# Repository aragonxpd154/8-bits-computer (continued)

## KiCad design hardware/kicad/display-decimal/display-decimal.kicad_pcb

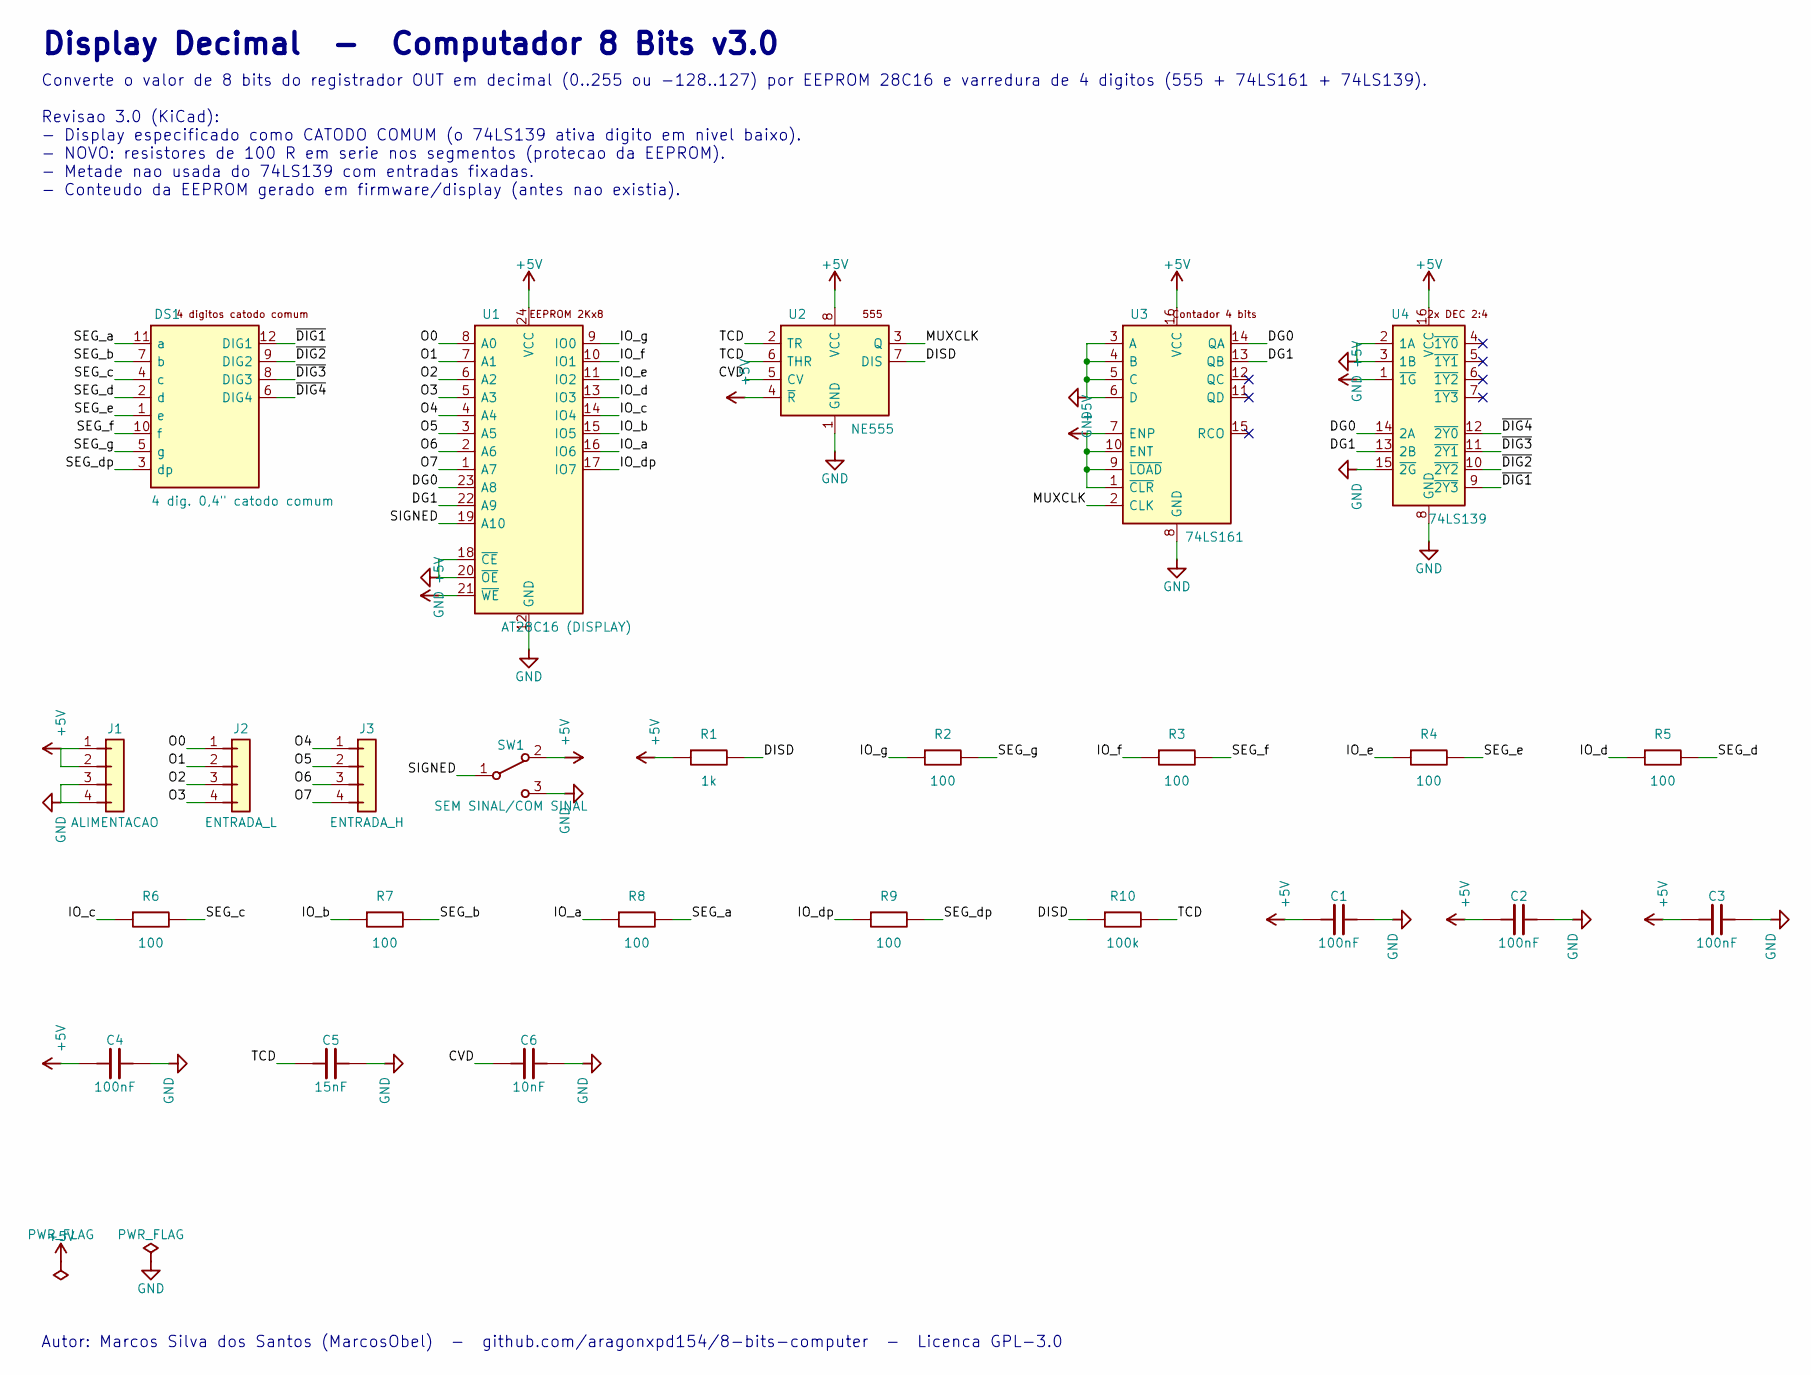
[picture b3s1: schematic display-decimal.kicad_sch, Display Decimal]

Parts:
C1, C2, C3, C4: 100nF; C_Disc_D5.0mm_W2.5mm_P5.00mm
C5: 15nF; C_Disc_D5.0mm_W2.5mm_P5.00mm
C6: 10nF; C_Disc_D5.0mm_W2.5mm_P5.00mm
DS1: 4 dig. 0,4" catodo comum; Display_7seg_4dig_0.4in
J1: ALIMENTACAO; PinHeader_1x04_P2.54mm_Vertical
J2: ENTRADA_L; PinHeader_1x04_P2.54mm_Vertical
J3: ENTRADA_H; PinHeader_1x04_P2.54mm_Vertical
R1: 1k; R_Axial_DIN0207_L6.3mm_D2.5mm_P10.16mm_Horizontal
R2, R3, R4, R5, R6, R7, R8, R9: 100; R_Axial_DIN0207_L6.3mm_D2.5mm_P10.16mm_Horizontal
R10: 100k; R_Axial_DIN0207_L6.3mm_D2.5mm_P10.16mm_Horizontal
SW1: SEM SINAL/COM SINAL; SW_Slide-03_Wuerth-WS-SLTV_10x2.5x6.4_P2.54mm
U1: AT28C16 (DISPLAY); DIP-24_W15.24mm_LongPads
U2: NE555; DIP-8_W7.62mm_LongPads
U3: 74LS161; DIP-16_W7.62mm_LongPads
U4: 74LS139; DIP-16_W7.62mm_LongPads

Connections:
+5V: C1.1, C2.1, C3.1, C4.1, J1.1, J1.2, R1.1, SW1.2 (A), U1.21 (~WE), U1.24 (VCC), U2.4 (~R), U2.8 (VCC), U3.1 (~CLR), U3.7 (ENP), U3.9 (~LOAD), U3.10 (ENT), U3.16 (VCC), U4.1 (~1G), U4.16 (VCC)
CVD: C6.1, U2.5 (CV)
DG0: U1.23 (A8), U3.14 (QA), U4.14 (2A)
DG1: U1.22 (A9), U3.13 (QB), U4.13 (2B)
DISD: R1.2, R10.1, U2.7 (DIS)
GND: C1.2, C2.2, C3.2, C4.2, C5.2, C6.2, J1.3, J1.4, SW1.3 (B), U1.12 (GND), U1.18 (~CE), U1.20 (~OE), U2.1 (GND), U3.3 (A), U3.4 (B), U3.5 (C), U3.6 (D), U3.8 (GND), U4.2 (1A), U4.3 (1B), U4.8 (GND), U4.15 (~2G)
IO_a: R8.1, U1.16 (IO6)
IO_b: R7.1, U1.15 (IO5)
IO_c: R6.1, U1.14 (IO4)
IO_d: R5.1, U1.13 (IO3)
IO_dp: R9.1, U1.17 (IO7)
IO_e: R4.1, U1.11 (IO2)
IO_f: R3.1, U1.10 (IO1)
IO_g: R2.1, U1.9 (IO0)
MUXCLK: U2.3 (Q), U3.2 (CLK)
O0: J2.1, U1.8 (A0)
O1: J2.2, U1.7 (A1)
O2: J2.3, U1.6 (A2)
O3: J2.4, U1.5 (A3)
O4: J3.1, U1.4 (A4)
O5: J3.2, U1.3 (A5)
O6: J3.3, U1.2 (A6)
O7: J3.4, U1.1 (A7)
SEG_a: DS1.11 (a), R8.2
SEG_b: DS1.7 (b), R7.2
SEG_c: DS1.4 (c), R6.2
SEG_d: DS1.2 (d), R5.2
SEG_dp: DS1.3 (dp), R9.2
SEG_e: DS1.1 (e), R4.2
SEG_f: DS1.10 (f), R3.2
SEG_g: DS1.5 (g), R2.2
SIGNED: SW1.1 (COM), U1.19 (A10)
TCD: C5.1, R10.2, U2.2 (TR), U2.6 (THR)
~DIG1: DS1.12 (DIG1), U4.9 (~2Y3)
~DIG2: DS1.9 (DIG2), U4.10 (~2Y2)
~DIG3: DS1.8 (DIG3), U4.11 (~2Y1)
~DIG4: DS1.6 (DIG4), U4.12 (~2Y0)

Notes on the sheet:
Display Decimal - Computador 8 Bits v3.0
Converte o valor de 8 bits do registrador OUT em decimal (0..255 ou -128..127) por EEPROM 28C16 e varredura de 4 digitos (555 + 74LS161 + 74LS139). Revisao 3.0 (KiCad): - Display especificado como CATODO COMUM (o 74LS139 ativa digito em nivel baixo). - NOVO: resistores de 100 R em serie nos segment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
Autor: Marcos Silva dos Santos (MarcosObel) - github.com/aragonxpd154/8-bits-computer - Licenca GPL-3.0

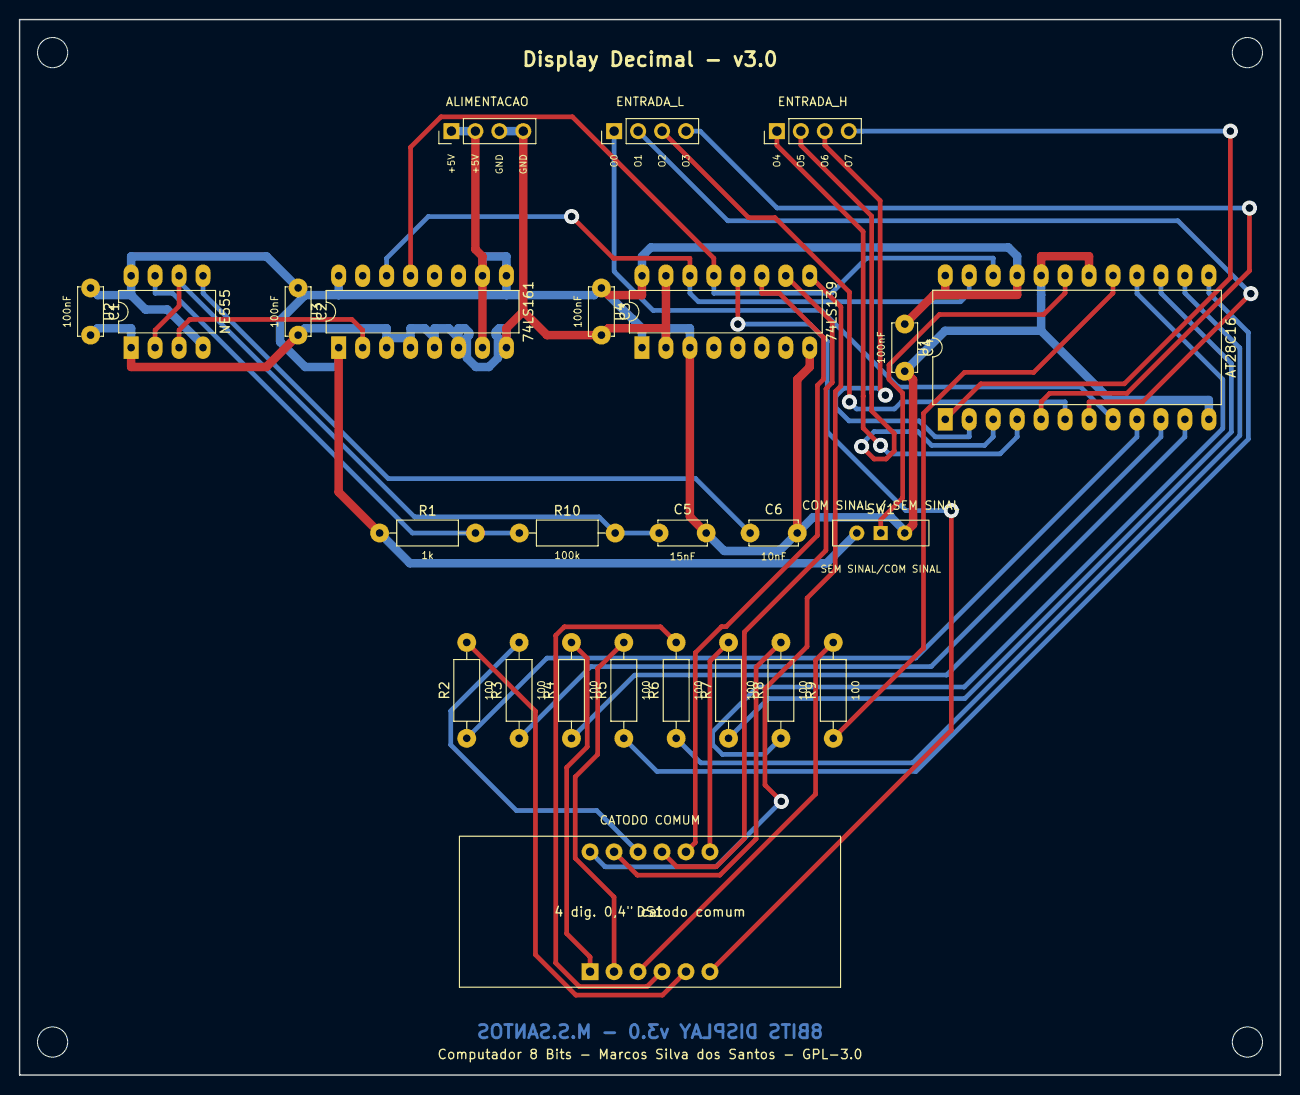
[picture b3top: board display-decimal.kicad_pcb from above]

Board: 2 copper layers, 133.7 x 111.9 mm, 29 parts (0 on the bottom side), 37 nets.

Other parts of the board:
H1, H2, H3, H4: MountingHole_3.2mm_M3

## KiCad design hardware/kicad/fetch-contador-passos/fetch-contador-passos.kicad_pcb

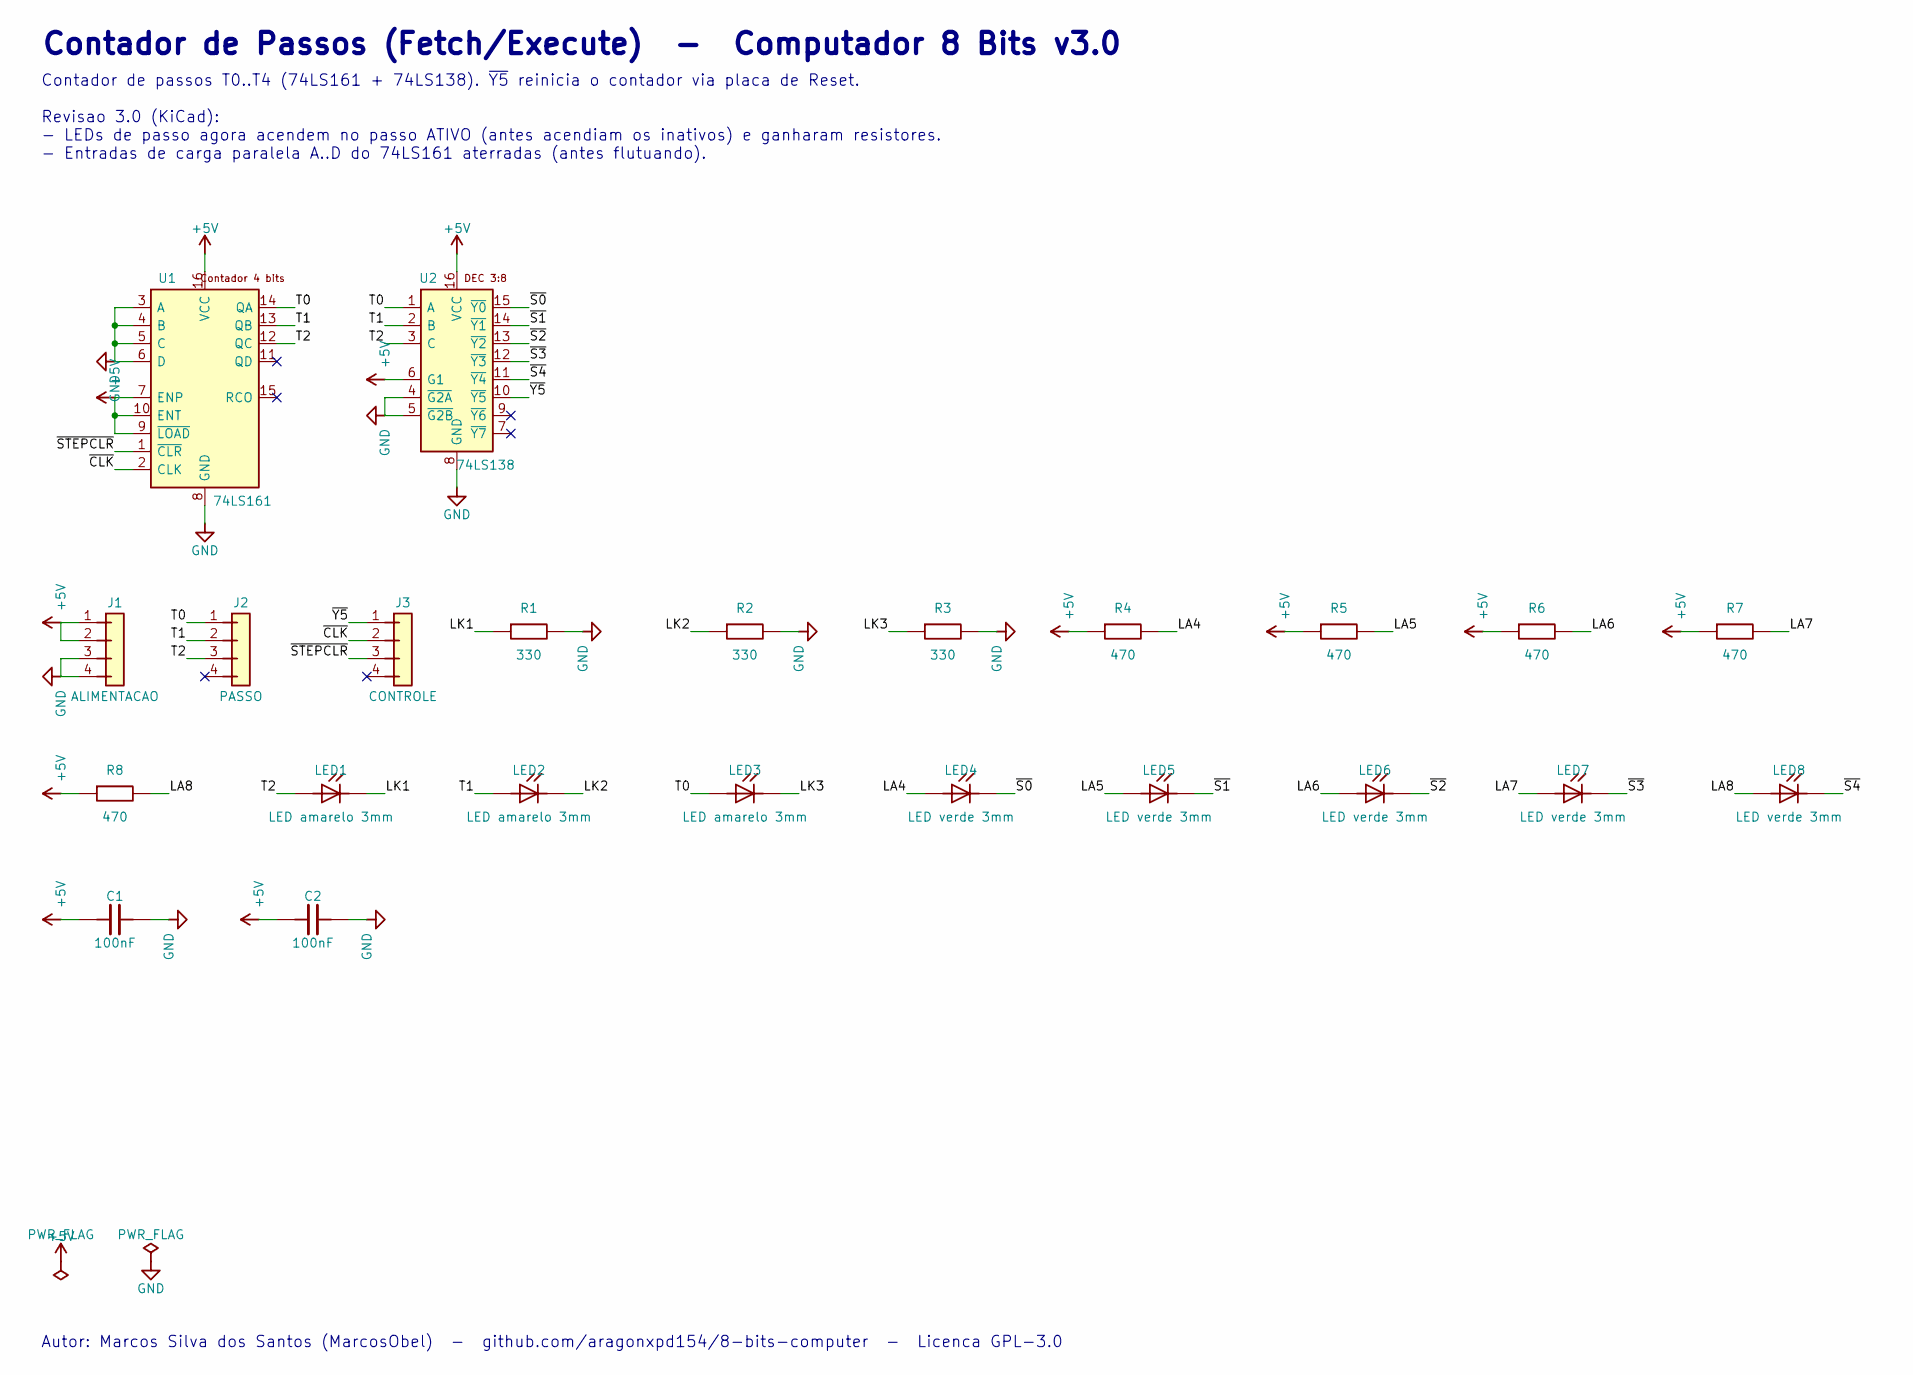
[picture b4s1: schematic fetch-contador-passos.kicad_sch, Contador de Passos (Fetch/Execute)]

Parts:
C1, C2: 100nF; C_Disc_D5.0mm_W2.5mm_P5.00mm
J1: ALIMENTACAO; PinHeader_1x04_P2.54mm_Vertical
J2: PASSO; PinHeader_1x04_P2.54mm_Vertical
J3: CONTROLE; PinHeader_1x04_P2.54mm_Vertical
LED1, LED2, LED3: LED amarelo 3mm; LED_D3.0mm
LED4, LED5, LED6, LED7, LED8: LED verde 3mm; LED_D3.0mm
R1, R2, R3: 330; R_Axial_DIN0207_L6.3mm_D2.5mm_P10.16mm_Horizontal
R4, R5, R6, R7, R8: 470; R_Axial_DIN0207_L6.3mm_D2.5mm_P10.16mm_Horizontal
U1: 74LS161; DIP-16_W7.62mm_LongPads
U2: 74LS138; DIP-16_W7.62mm_LongPads

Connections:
+5V: C1.1, C2.1, J1.1, J1.2, R4.1, R5.1, R6.1, R7.1, R8.1, U1.7 (ENP), U1.9 (~LOAD), U1.10 (ENT), U1.16 (VCC), U2.6 (G1), U2.16 (VCC)
GND: C1.2, C2.2, J1.3, J1.4, R1.2, R2.2, R3.2, U1.3 (A), U1.4 (B), U1.5 (C), U1.6 (D), U1.8 (GND), U2.4 (~G2A), U2.5 (~G2B), U2.8 (GND)
LA4: LED4.2 (A), R4.2
LA5: LED5.2 (A), R5.2
LA6: LED6.2 (A), R6.2
LA7: LED7.2 (A), R7.2
LA8: LED8.2 (A), R8.2
LK1: LED1.1 (K), R1.1
LK2: LED2.1 (K), R2.1
LK3: LED3.1 (K), R3.1
T0: J2.1, LED3.2 (A), U1.14 (QA), U2.1 (A)
T1: J2.2, LED2.2 (A), U1.13 (QB), U2.2 (B)
T2: J2.3, LED1.2 (A), U1.12 (QC), U2.3 (C)
~CLK: J3.2, U1.2 (CLK)
~S0: LED4.1 (K), U2.15 (~Y0)
~S1: LED5.1 (K), U2.14 (~Y1)
~S2: LED6.1 (K), U2.13 (~Y2)
~S3: LED7.1 (K), U2.12 (~Y3)
~S4: LED8.1 (K), U2.11 (~Y4)
~STEPCLR: J3.3, U1.1 (~CLR)
~Y5: J3.1, U2.10 (~Y5)

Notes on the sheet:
Contador de Passos (Fetch/Execute) - Computador 8 Bits v3.0
Contador de passos T0..T4 (74LS161 + 74LS138). ~{Y5} reinicia o contador via placa de Reset. Revisao 3.0 (KiCad): - LEDs de passo agora acendem no passo ATIVO (antes acendiam os inativos) e ganharam resistores. - Entradas de carga paralela A..D do 74LS161 aterradas (antes flutuando).
Autor: Marcos Silva dos Santos (MarcosObel) - github.com/aragonxpd154/8-bits-computer - Licenca GPL-3.0

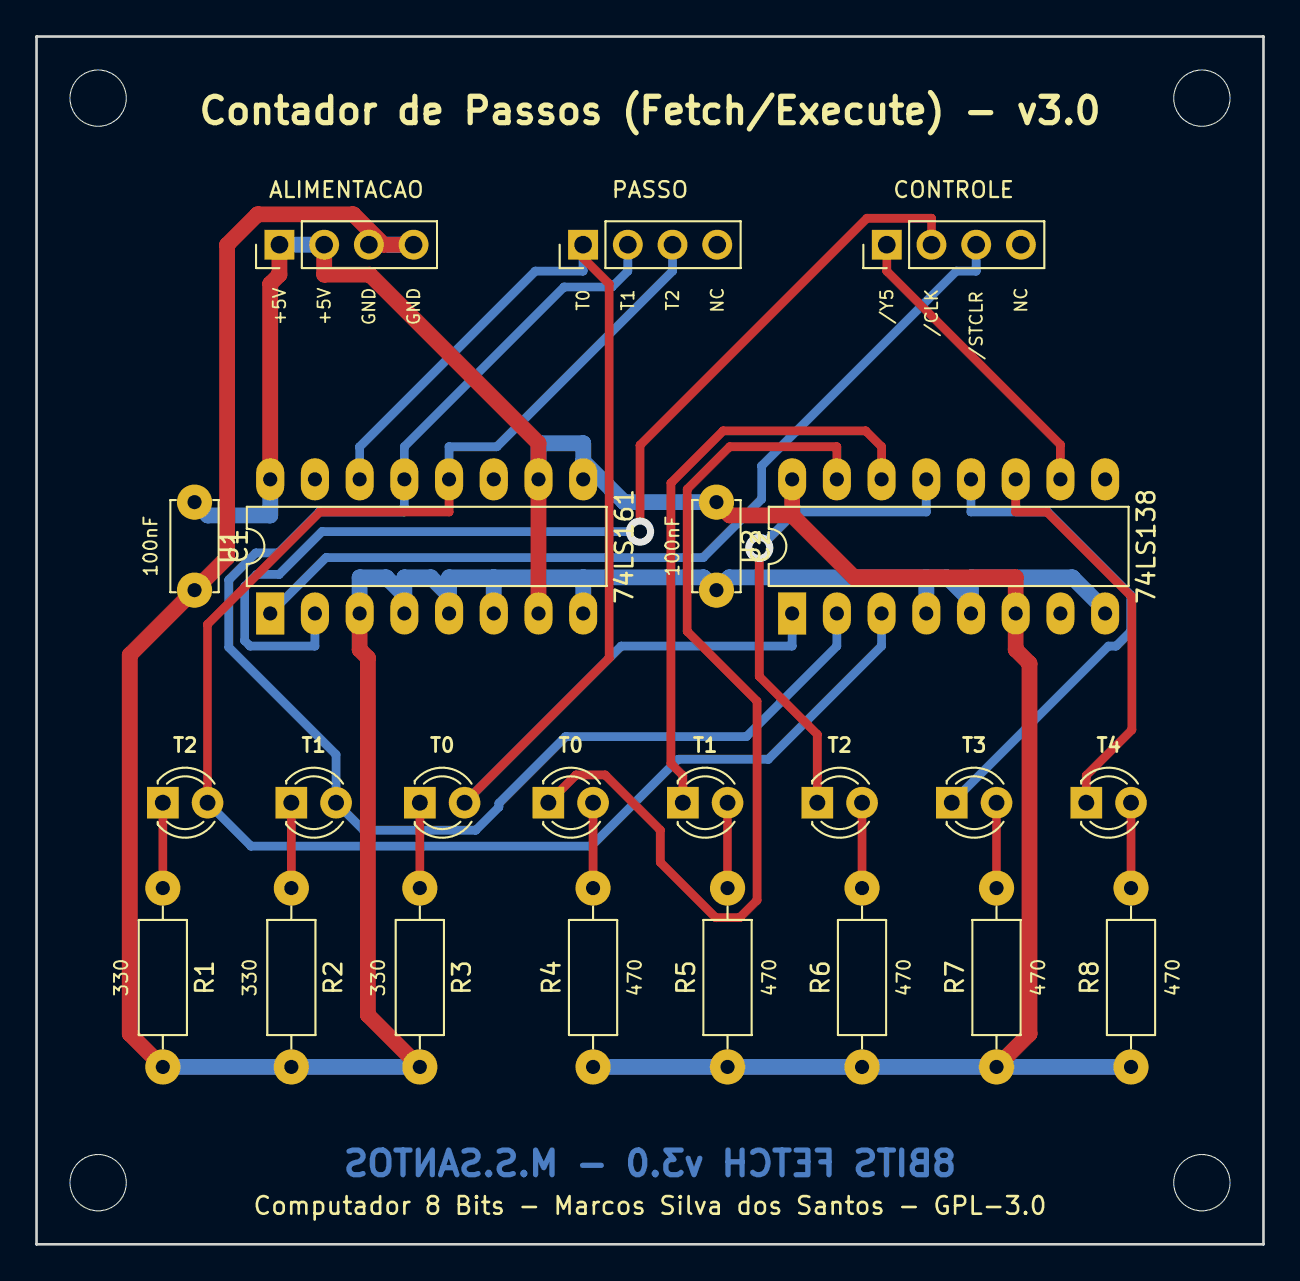
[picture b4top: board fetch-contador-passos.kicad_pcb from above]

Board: 2 copper layers, 69.7 x 68.6 mm, 27 parts (0 on the bottom side), 21 nets.

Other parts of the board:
H1, H2, H3, H4: MountingHole_3.2mm_M3

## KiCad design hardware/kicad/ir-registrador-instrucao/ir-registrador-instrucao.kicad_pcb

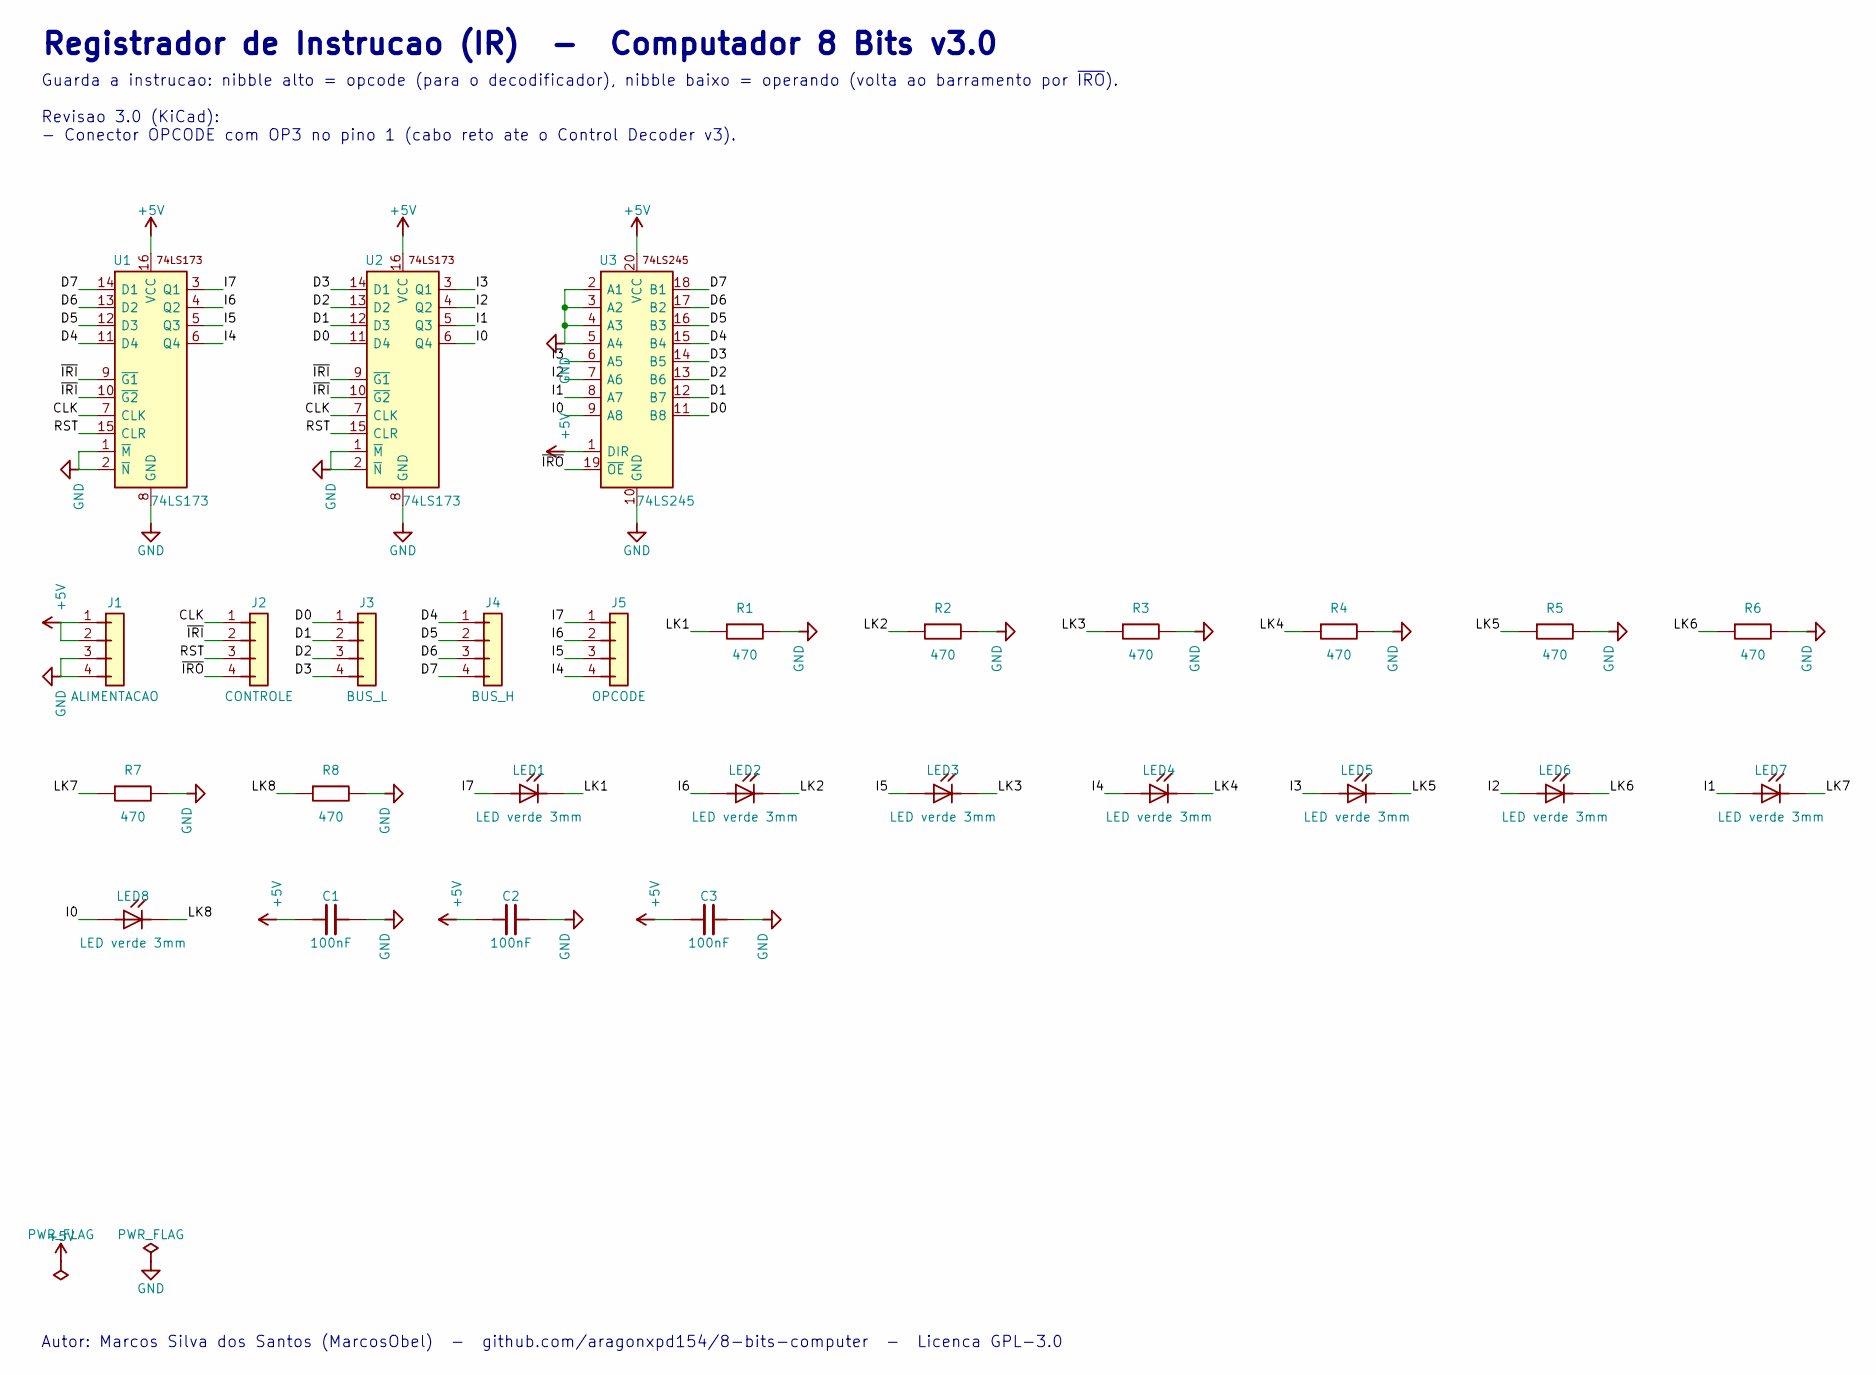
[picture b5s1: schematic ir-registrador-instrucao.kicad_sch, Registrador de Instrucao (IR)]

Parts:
C1, C2, C3: 100nF; C_Disc_D5.0mm_W2.5mm_P5.00mm
J1: ALIMENTACAO; PinHeader_1x04_P2.54mm_Vertical
J2: CONTROLE; PinHeader_1x04_P2.54mm_Vertical
J3: BUS_L; PinHeader_1x04_P2.54mm_Vertical
J4: BUS_H; PinHeader_1x04_P2.54mm_Vertical
J5: OPCODE; PinHeader_1x04_P2.54mm_Vertical
LED1, LED2, LED3, LED4, LED5, LED6, LED7, LED8: LED verde 3mm; LED_D3.0mm
R1, R2, R3, R4, R5, R6, R7, R8: 470; R_Axial_DIN0207_L6.3mm_D2.5mm_P10.16mm_Horizontal
U1, U2: 74LS173; DIP-16_W7.62mm_LongPads
U3: 74LS245; DIP-20_W7.62mm_LongPads

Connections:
+5V: C1.1, C2.1, C3.1, J1.1, J1.2, U1.16 (VCC), U2.16 (VCC), U3.1 (DIR), U3.20 (VCC)
CLK: J2.1, U1.7 (CLK), U2.7 (CLK)
D0: J3.1, U2.11 (D4), U3.11 (B8)
D1: J3.2, U2.12 (D3), U3.12 (B7)
D2: J3.3, U2.13 (D2), U3.13 (B6)
D3: J3.4, U2.14 (D1), U3.14 (B5)
D4: J4.1, U1.11 (D4), U3.15 (B4)
D5: J4.2, U1.12 (D3), U3.16 (B3)
D6: J4.3, U1.13 (D2), U3.17 (B2)
D7: J4.4, U1.14 (D1), U3.18 (B1)
GND: C1.2, C2.2, C3.2, J1.3, J1.4, R1.2, R2.2, R3.2, R4.2, R5.2, R6.2, R7.2, R8.2, U1.1 (~M), U1.2 (~N), U1.8 (GND), U2.1 (~M), U2.2 (~N), U2.8 (GND), U3.2 (A1), U3.3 (A2), U3.4 (A3), U3.5 (A4), U3.10 (GND)
I0: LED8.2 (A), U2.6 (Q4), U3.9 (A8)
I1: LED7.2 (A), U2.5 (Q3), U3.8 (A7)
I2: LED6.2 (A), U2.4 (Q2), U3.7 (A6)
I3: LED5.2 (A), U2.3 (Q1), U3.6 (A5)
I4: J5.4, LED4.2 (A), U1.6 (Q4)
I5: J5.3, LED3.2 (A), U1.5 (Q3)
I6: J5.2, LED2.2 (A), U1.4 (Q2)
I7: J5.1, LED1.2 (A), U1.3 (Q1)
LK1: LED1.1 (K), R1.1
LK2: LED2.1 (K), R2.1
LK3: LED3.1 (K), R3.1
LK4: LED4.1 (K), R4.1
LK5: LED5.1 (K), R5.1
LK6: LED6.1 (K), R6.1
LK7: LED7.1 (K), R7.1
LK8: LED8.1 (K), R8.1
RST: J2.3, U1.15 (CLR), U2.15 (CLR)
~IRI: J2.2, U1.9 (~G1), U1.10 (~G2), U2.9 (~G1), U2.10 (~G2)
~IRO: J2.4, U3.19 (~OE)

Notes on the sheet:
Registrador de Instrucao (IR) - Computador 8 Bits v3.0
Guarda a instrucao: nibble alto = opcode (para o decodificador), nibble baixo = operando (volta ao barramento por ~{IRO}). Revisao 3.0 (KiCad): - Conector OPCODE com OP3 no pino 1 (cabo reto ate o Control Decoder v3).
Autor: Marcos Silva dos Santos (MarcosObel) - github.com/aragonxpd154/8-bits-computer - Licenca GPL-3.0

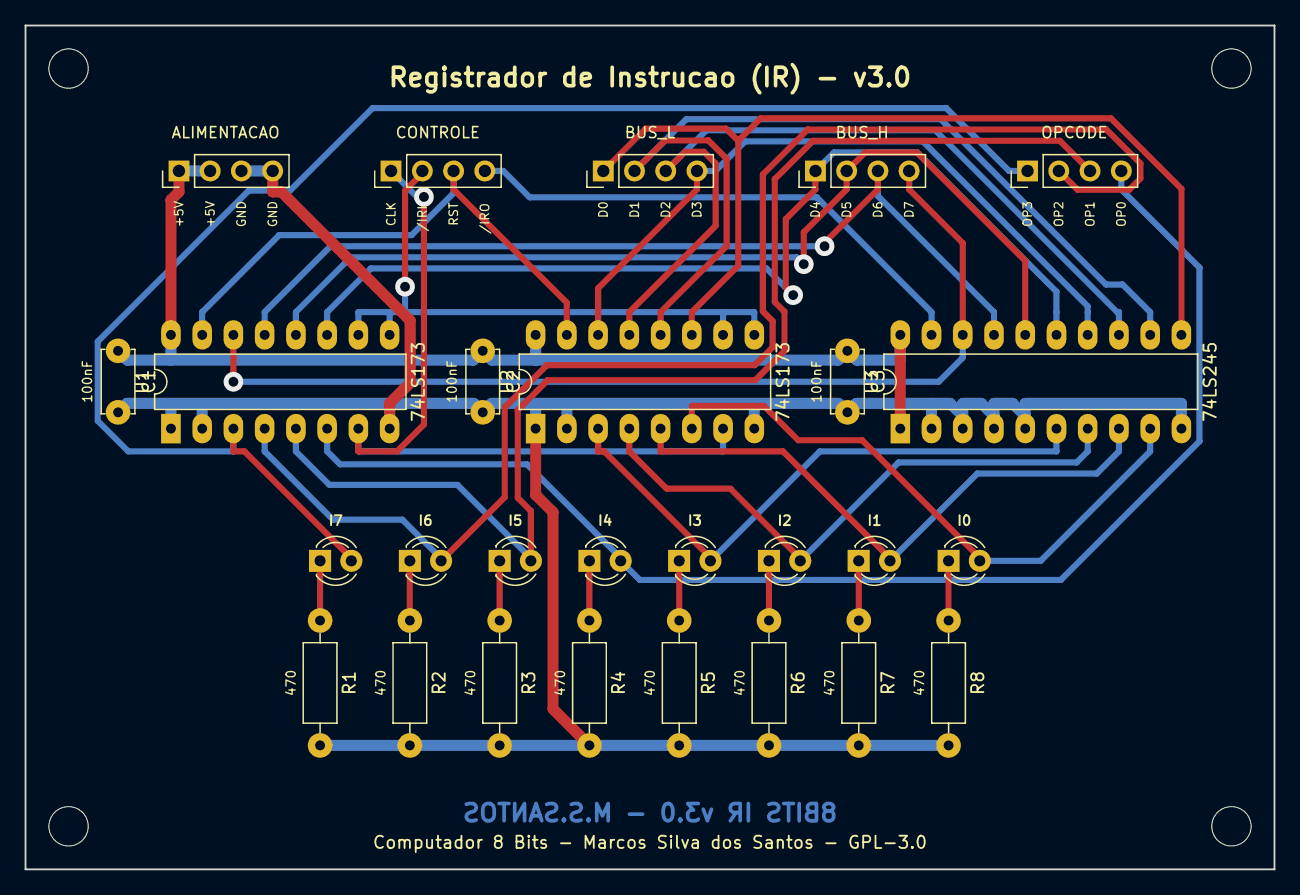
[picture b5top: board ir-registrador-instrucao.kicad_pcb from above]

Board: 2 copper layers, 101.5 x 68.6 mm, 31 parts (0 on the bottom side), 30 nets.

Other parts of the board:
H1, H2, H3, H4: MountingHole_3.2mm_M3

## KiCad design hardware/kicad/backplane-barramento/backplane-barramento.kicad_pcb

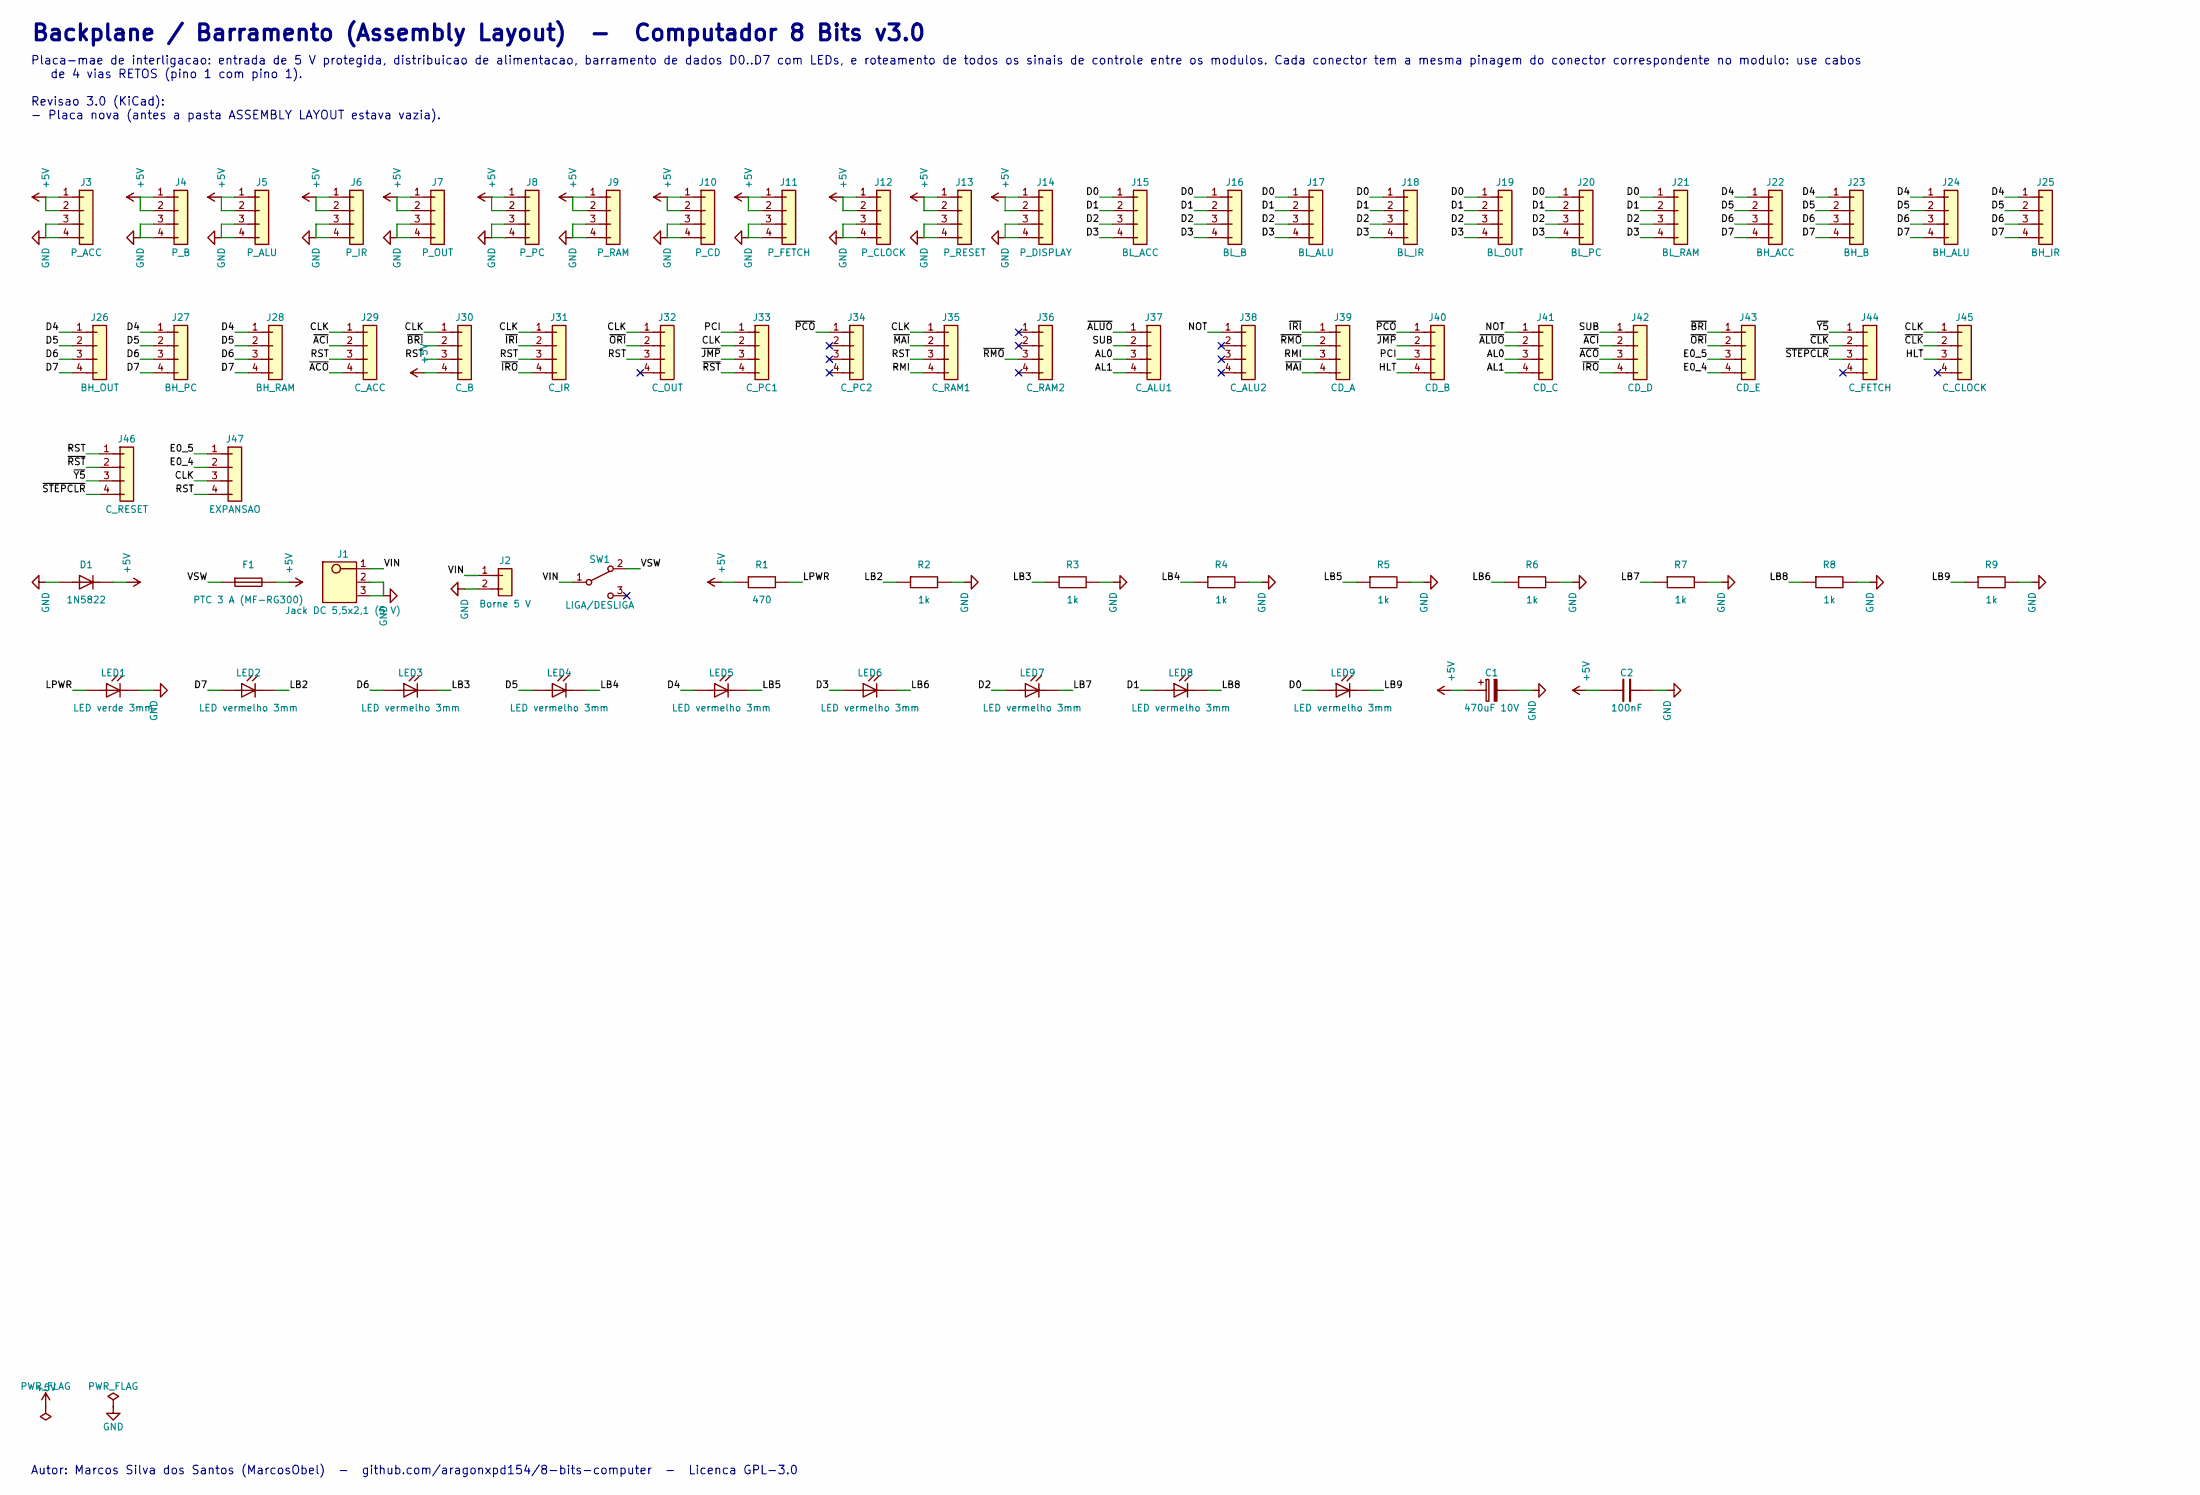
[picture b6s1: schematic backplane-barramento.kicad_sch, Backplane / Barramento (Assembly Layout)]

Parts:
C1: 470uF 10V; CP_Radial_D10.0mm_P5.00mm
C2: 100nF; C_Disc_D5.0mm_W2.5mm_P5.00mm
D1: 1N5822; D_DO-201AD_P15.24mm_Horizontal
F1: PTC 3 A (MF-RG300); Fuse_Bourns_MF-RG300
J1: Jack DC 5,5x2,1 (5 V); BarrelJack_Horizontal
J2: Borne 5 V; TerminalBlock_bornier-2_P5.08mm
J3: P_ACC; PinHeader_1x04_P2.54mm_Vertical
J4: P_B; PinHeader_1x04_P2.54mm_Vertical
J5: P_ALU; PinHeader_1x04_P2.54mm_Vertical
J6: P_IR; PinHeader_1x04_P2.54mm_Vertical
J7: P_OUT; PinHeader_1x04_P2.54mm_Vertical
J8: P_PC; PinHeader_1x04_P2.54mm_Vertical
J9: P_RAM; PinHeader_1x04_P2.54mm_Vertical
J10: P_CD; PinHeader_1x04_P2.54mm_Vertical
J11: P_FETCH; PinHeader_1x04_P2.54mm_Vertical
J12: P_CLOCK; PinHeader_1x04_P2.54mm_Vertical
J13: P_RESET; PinHeader_1x04_P2.54mm_Vertical
J14: P_DISPLAY; PinHeader_1x04_P2.54mm_Vertical
J15: BL_ACC; PinHeader_1x04_P2.54mm_Vertical
J16: BL_B; PinHeader_1x04_P2.54mm_Vertical
J17: BL_ALU; PinHeader_1x04_P2.54mm_Vertical
J18: BL_IR; PinHeader_1x04_P2.54mm_Vertical
J19: BL_OUT; PinHeader_1x04_P2.54mm_Vertical
J20: BL_PC; PinHeader_1x04_P2.54mm_Vertical
J21: BL_RAM; PinHeader_1x04_P2.54mm_Vertical
J22: BH_ACC; PinHeader_1x04_P2.54mm_Vertical
J23: BH_B; PinHeader_1x04_P2.54mm_Vertical
J24: BH_ALU; PinHeader_1x04_P2.54mm_Vertical
J25: BH_IR; PinHeader_1x04_P2.54mm_Vertical
J26: BH_OUT; PinHeader_1x04_P2.54mm_Vertical
J27: BH_PC; PinHeader_1x04_P2.54mm_Vertical
J28: BH_RAM; PinHeader_1x04_P2.54mm_Vertical
J29: C_ACC; PinHeader_1x04_P2.54mm_Vertical
J30: C_B; PinHeader_1x04_P2.54mm_Vertical
J31: C_IR; PinHeader_1x04_P2.54mm_Vertical
J32: C_OUT; PinHeader_1x04_P2.54mm_Vertical
J33: C_PC1; PinHeader_1x04_P2.54mm_Vertical
J34: C_PC2; PinHeader_1x04_P2.54mm_Vertical
J35: C_RAM1; PinHeader_1x04_P2.54mm_Vertical
J36: C_RAM2; PinHeader_1x04_P2.54mm_Vertical
J37: C_ALU1; PinHeader_1x04_P2.54mm_Vertical
J38: C_ALU2; PinHeader_1x04_P2.54mm_Vertical
J39: CD_A; PinHeader_1x04_P2.54mm_Vertical
J40: CD_B; PinHeader_1x04_P2.54mm_Vertical
J41: CD_C; PinHeader_1x04_P2.54mm_Vertical
J42: CD_D; PinHeader_1x04_P2.54mm_Vertical
J43: CD_E; PinHeader_1x04_P2.54mm_Vertical
J44: C_FETCH; PinHeader_1x04_P2.54mm_Vertical
J45: C_CLOCK; PinHeader_1x04_P2.54mm_Vertical
J46: C_RESET; PinHeader_1x04_P2.54mm_Vertical
J47: EXPANSAO; PinHeader_1x04_P2.54mm_Vertical
LED1: LED verde 3mm; LED_D3.0mm
LED2, LED3, LED4, LED5, LED6, LED7, LED8, LED9: LED vermelho 3mm; LED_D3.0mm
R1: 470; R_Axial_DIN0207_L6.3mm_D2.5mm_P10.16mm_Horizontal
R2, R3, R4, R5, R6, R7, R8, R9: 1k; R_Axial_DIN0207_L6.3mm_D2.5mm_P10.16mm_Horizontal
SW1: LIGA/DESLIGA; SW_Slide-03_Wuerth-WS-SLTV_10x2.5x6.4_P2.54mm

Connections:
+5V: C1.1, C2.1, D1.1 (K), F1.2, J3.1, J3.2, J4.1, J4.2, J5.1, J5.2, J6.1, J6.2, J7.1, J7.2, J8.1, J8.2, J9.1, J9.2, J10.1, J10.2, J11.1, J11.2, J12.1, J12.2, J13.1, J13.2, J14.1, J14.2, J30.4, R1.1
AL0: J37.3, J41.3
AL1: J37.4, J41.4
CLK: J29.1, J30.1, J31.1, J32.1, J33.2, J35.1, J45.1, J47.3
D0: J15.1, J16.1, J17.1, J18.1, J19.1, J20.1, J21.1, LED9.2 (A)
D1: J15.2, J16.2, J17.2, J18.2, J19.2, J20.2, J21.2, LED8.2 (A)
D2: J15.3, J16.3, J17.3, J18.3, J19.3, J20.3, J21.3, LED7.2 (A)
D3: J15.4, J16.4, J17.4, J18.4, J19.4, J20.4, J21.4, LED6.2 (A)
D4: J22.1, J23.1, J24.1, J25.1, J26.1, J27.1, J28.1, LED5.2 (A)
D5: J22.2, J23.2, J24.2, J25.2, J26.2, J27.2, J28.2, LED4.2 (A)
D6: J22.3, J23.3, J24.3, J25.3, J26.3, J27.3, J28.3, LED3.2 (A)
D7: J22.4, J23.4, J24.4, J25.4, J26.4, J27.4, J28.4, LED2.2 (A)
E0_4: J43.4, J47.2
E0_5: J43.3, J47.1
GND: C1.2, C2.2, D1.2 (A), J1.2 (-), J1.3 (SW), J2.2, J3.3, J3.4, J4.3, J4.4, J5.3, J5.4, J6.3, J6.4, J7.3, J7.4, J8.3, J8.4, J9.3, J9.4, J10.3, J10.4, J11.3, J11.4, J12.3, J12.4, J13.3, J13.4, J14.3, J14.4, LED1.1 (K), R2.2, R3.2, R4.2, R5.2, R6.2, R7.2, R8.2, R9.2
HLT: J40.4, J45.3
LB2: LED2.1 (K), R2.1
LB3: LED3.1 (K), R3.1
LB4: LED4.1 (K), R4.1
LB5: LED5.1 (K), R5.1
LB6: LED6.1 (K), R6.1
LB7: LED7.1 (K), R7.1
LB8: LED8.1 (K), R8.1
LB9: LED9.1 (K), R9.1
LPWR: LED1.2 (A), R1.2
NOT: J38.1, J41.1
PCI: J33.1, J40.3
RMI: J35.4, J39.3
RST: J29.3, J30.3, J31.3, J32.3, J35.3, J46.1, J47.4
SUB: J37.2, J42.1
VIN: J1.1 (+), J2.1, SW1.1 (COM)
VSW: F1.1, SW1.2 (A)
~ACI: J29.2, J42.2
~ACO: J29.4, J42.3
~ALUO: J37.1, J41.2
~BRI: J30.2, J43.1
~CLK: J44.2, J45.2
~IRI: J31.2, J39.1
~IRO: J31.4, J42.4
~JMP: J33.3, J40.2
~MAI: J35.2, J39.4
~ORI: J32.2, J43.2
~PCO: J34.1, J40.1
~RMO: J36.3, J39.2
~RST: J33.4, J46.2
~STEPCLR: J44.3, J46.4
~Y5: J44.1, J46.3

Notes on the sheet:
Backplane / Barramento (Assembly Layout) - Computador 8 Bits v3.0
Placa-mae de interligacao: entrada de 5 V protegida, distribuicao de alimentacao, barramento de dados D0..D7 com LEDs, e roteamento de todos os sinais de controle entre os modulos. Cada conector tem a mesma pinagem do conector correspondente no modulo: use cabos de 4 vias RETOS (pino 1 com pino 1).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
Autor: Marcos Silva dos Santos (MarcosObel) - github.com/aragonxpd154/8-bits-computer - Licenca GPL-3.0
